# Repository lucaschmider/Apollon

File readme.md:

# Apollon - Dayli Briefing

Please consult the detailed [documentation](Docs/Projektdokumentation.md) for more information.

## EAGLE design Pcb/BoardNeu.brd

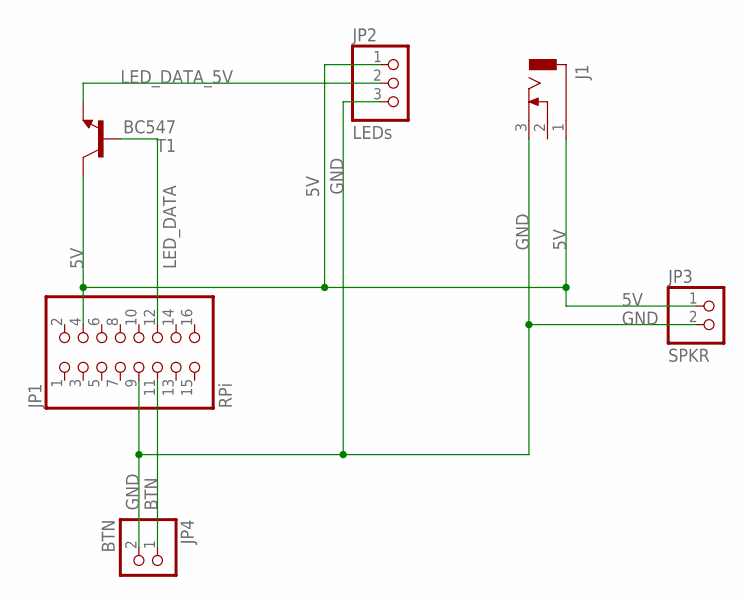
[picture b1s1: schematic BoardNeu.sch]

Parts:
J1: DCJ0303
JP1: RPi; 2X08
JP2: LEDs; 1X03
JP3: SPKR; 1X02
JP4: BTN; 1X02
T1: BC547; TO92

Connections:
5V: J1.1, JP1.4, JP2.1, JP3.1, T1.3 (C)
BTN: JP1.11, JP4.1
GND: J1.3, JP1.9, JP2.3, JP3.2, JP4.2
LED_DATA: JP1.12, T1.2 (B)
LED_DATA_5V: JP2.2, T1.1 (E)

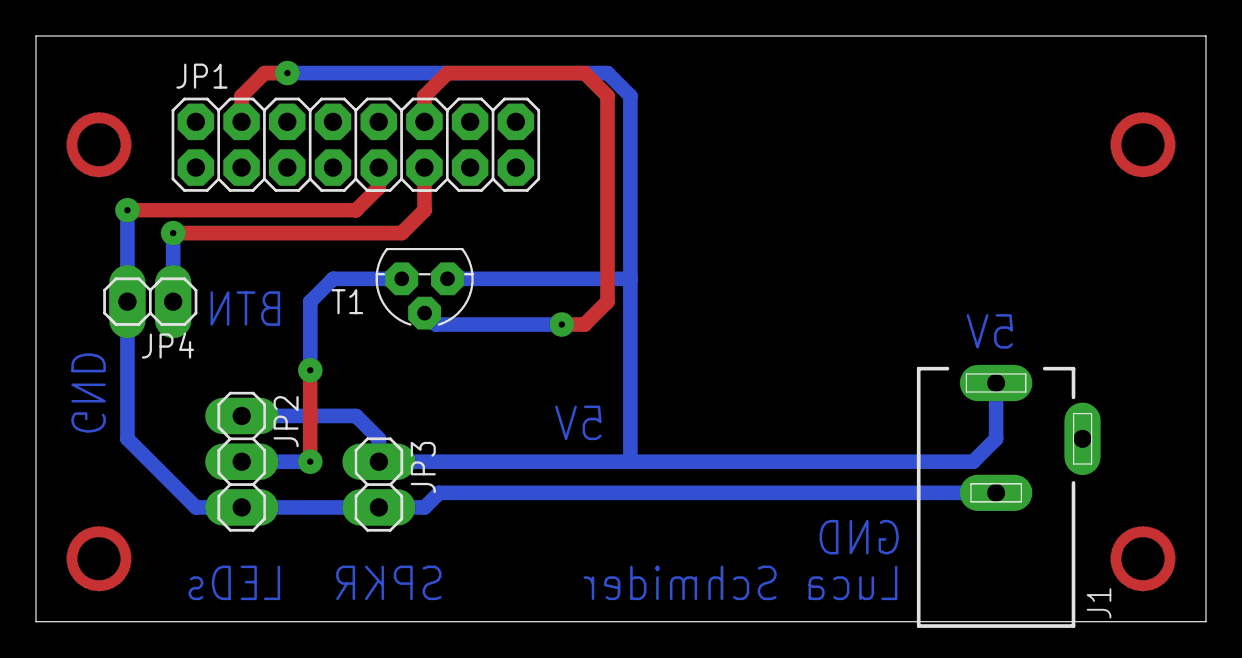
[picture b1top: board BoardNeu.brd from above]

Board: 2 copper layers, 65.0 x 32.5 mm, 6 parts (0 on the bottom side), 5 nets.

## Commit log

2020-08-01 Created project
2020-08-01 Added ConsoleConsumer
2020-08-01 Implemented Broadcast
2020-08-01 Implemented TriggerBase
2020-08-01 Implemented timetrigger
2020-08-01 using trigger in main py
2020-08-01 debounced timetrigger
2020-08-01 implemented basic report generator
2020-08-01 linked report generator with existing application
2020-08-01 Implemented data fetching from api
2020-08-01 implemented unit and time conversion
2020-08-02 Added RKI Case App for backup
2020-08-03 implemented generation of speech
2020-08-03 implemented audio playback
2020-08-03 updated gitinore
2020-08-17 implemented button trigger
2020-08-17 added requirements
2020-08-21 added readme
2020-08-21 implemented led consumer hook
2020-08-21 fixed speech consumer
2020-08-26 speech consumer now runs synchronously
2020-08-26 improved imports
2020-08-26 updated led hook
2020-08-26 fixed led hook
2020-08-26 Added application ready hook
2020-08-26 extracted hardcoded configuration
2020-08-26 updated console log & type hints
2020-08-26 fixed time trigger
2020-08-26 moved weather report generator
2020-08-26 implemented covid report generator
2020-08-29 updated animations
2020-08-29 fixed hook
2020-08-29 updated config
2020-08-29 updated docs
2020-08-29 Updated Weather Report generator
2020-08-31 Fixed indentation
2020-09-02 Added Chapter for the housing
2020-09-28 updated documentation
2020-09-28 rendered documentation
